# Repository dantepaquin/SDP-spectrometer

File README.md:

# SDP-Spectrometer

This is the joint repository for the hardware and software for the UCSC EE SDP 2021 Spectrometer. 
The directory *kicad-libraries* contains all of the design files for the hardware, including the schematics, kicad projects, footprint & symbol libraries, and gerbers.
The directory *microcontroller-libraries* contains all of the software used by our spectrometer.

## Kicad Libraries
In our design, we used [KiCad v5.1.0](https://www.kicad.org/blog/2019/03/KiCad-5.1.0-Release/) to create libraries for footprints, symbols, schematics, and pcbs. Currently, the initial designs are in their first revision, and we have fabricated prototypes to be tested.

While our design uses five separate boards connected with wires, all designs are located within a single KiCad project, "main.pro."

### Overview of directories:
#### Adafruit-PowerBoost-1000C-master/
Our design uses an existing power delivery board, and this folder contains the physical design documents that we referenced and used in our own.

#### Backup/
An almost-empty folder used for managing local backups and versioining. Can be removed.

#### RN4678dev/
This contains a kicad project and its design files for a development board, opening the SMD footprint to machine headers. These are not necessary for the final design.

#### Renders/
This contains PDF views of the current PCBs, shown with a small selection of layers.

#### SC70-Dev/
This is a development board used for the SC70 footprint, allowing breadboard verification of our systems. This contains a kicad project with the scematic and PCB files.

#### Separate/
This directory contains subdirectories for each of the five PCBs of our design, which allowed us to manufacture individual boards rather than the full set. This also includes the gerbers used to manufacture the initial run of boards. 

#### Wiring Diagram/
This was a development project to identify and plan the necessary connections between the components of our design. It exists for reference, and has no physical form.

#### spectrometer_core.pretty/
This is the footprint library directory, implementing the physical dimensions and connections of each device used in our design.

#### fp-lib-table
This file tells KiCad how to associate the symbols in our schematic with the footprints in spectrometer_core.pretty.

#### main-cache.lib
This file keeps track of all of the symbols used in the schematic.

#### main.kicad_pcb
This is the main PCB file, which is used to design and lay out the footprints into their physical form.

#### main.pro
**This is the main project file of the spectrometer.** Opening this with kicad will give you access to design and change the footprints, symbols, schematics, and PCBs of the design.

#### main.sch
This is the main schematic file, used to establish connections between the components of the design.

#### spectrometer_core.bck
This is a local backup of the spectrometer_core.dcm file, and can be removed.

#### spectrometer_core.dcm
This keeps track of any documentation we added to the symbol library.

#### spectrometer_core.lib
This is our main symbol library, used to represent the components as used on our schematic.

#### sym-lib-table
This keeps track of the symbol libraries used in the main project.

## Microcontroller Libraries

Our project uses a [TeensyLC](https://www.pjrc.com/teensy/teensyLC.html) running [Arduino](https://www.arduino.cc/en/software), and was developed in the Arduino IDE. This directory contains the code we were able to complete, and verious sketches of test programs.

### Overview of directories:

#### Bluetooth/
This directory contains the currnent state of the bluetooth library implementation. The files include CircularBuffer.c/h, used for UART communication; RN4678.cpp/h, the main library file for the RN4678 bluetooth module; and RN4678_Command.h, a file containing all of the available bluetooth commands.

#### Examples/
This directory includes arduino sketches used to verify both the hardware and minor software usage in our design. These will allow basic back-and-forth, following PC -> USB -> Teesny -> UART -> RN4678 -> Bluetooth -> Phone

#### TeesnyMain/
This is the main directory of code running on the TeensyLC, TeensyMain.ino, and includes state machines and libraries used in our design.  

#### Adafruit_SSD1306.cpp/h
This is an open library by Adafruit designed for our OLED screen, based on the SSD1306 driver IC.

#### FiniteStateMachine.cpp/h
This is an old backup of the driving state machine of our microcontroller. The updated version is in TeensyMain/

#### LED.cpp/h
These files are basic LED drivers for arduino, and can be ignored.

#### RN4678_Command.h
This is a backup of the same file located in Bluetooth/. Both files include usage documentation inside

#### TeensyMain.ino
This is an old backup of the main arduino sketch within TeensyMain/, and can be ignored.

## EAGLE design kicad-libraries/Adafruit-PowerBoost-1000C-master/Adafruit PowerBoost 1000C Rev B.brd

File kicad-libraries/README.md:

# Repository for KiCad Libraries and design

Individual design files (footprints & symbols) will go into part-specific subfolders in the "Separate" folder

KiCad organization basics:  
.LIB files store SCHEMATIC SYMBOLS  
.PRETTY folders store FOOTPRINT MODELS  
The two should be associated in their current form. 

Further work includes building basic building-block circuits so that integration is easier later on.

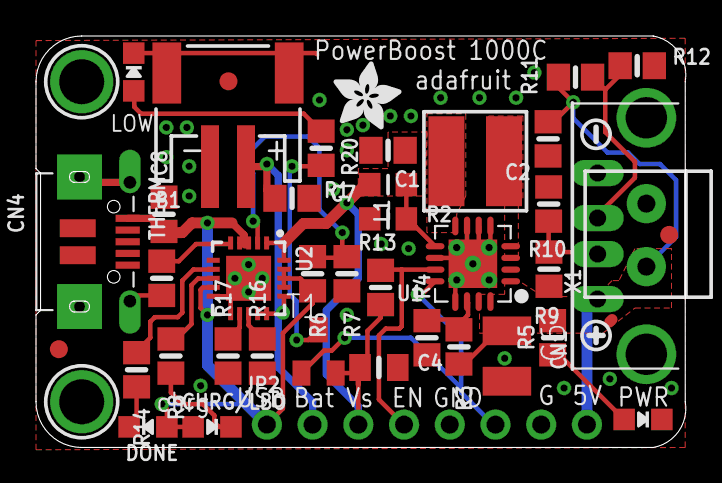
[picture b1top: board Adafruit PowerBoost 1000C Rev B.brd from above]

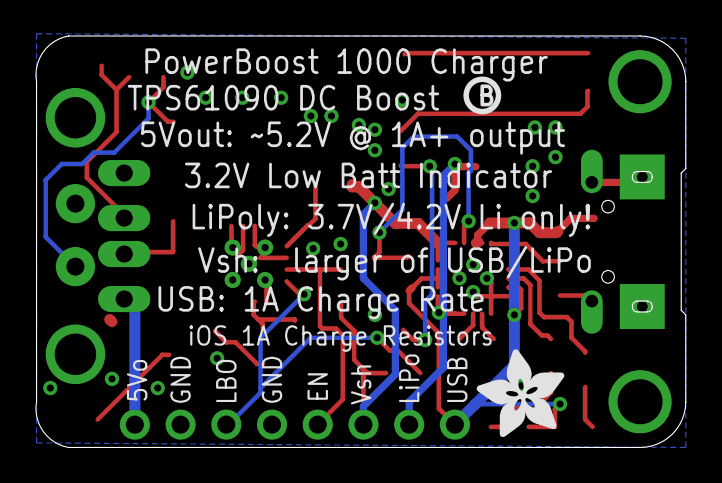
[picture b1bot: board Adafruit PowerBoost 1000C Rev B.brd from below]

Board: 2 copper layers, 36.1 x 22.9 mm, 47 parts (2 on the bottom side), 23 nets.

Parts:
B1: JST 2-PH; JSTPH2
C1, C7, C8: 10uF; 0805-NO
C2: 2.2uF; 0805-NO
C4: 0.1uF; 0805_10MGAP
C6: 100uF; C1210
CHRG/LBO: ORANGE; CHIPLED_0805_NOOUTLINE
CN1: USBA_FEMALE; USB_HOST-PTH
CN4: MicroUSB; 4UCONN_20329
DONE: GREEN; CHIPLED_0805_NOOUTLINE
FID1, FID2, FID3: FIDUCIAL""; FIDUCIAL_1MM
JP2: 1X08_ROUND
L1: 6.8uH; INDUCTOR_5X5MM_TDK_VLC5045
LED1: RED; CHIPLED_0805_NOOUTLINE
LED2: BLUE; CHIPLED_0805_NOOUTLINE
R1: 1.87M; _0805MP
R2: 340K; _0805MP
R3: 1.87M; 0805-NO
R4, R13: 200K; 0805-NO
R5, R8, R14, R20: 1K; 0805-NO
R6: 270K; 0805-NO
R7, R17: 100K; 0805-NO
R9: 43K; 0805-NO
R10: 49.9K; 0805-NO
R11: 75K 1%; 0805-NO
R12: 49.9K 1%; 0805-NO
R16: 1.0K; 0805-NO
T1: MMUN2133LT1G; SC59-BEC
THERM: 15K; 0805-NO
U1: TPS61090RSAR; PVQFN-16
U2: MCP73871; QFN20_4MM
U$10, U$11: MOUNTINGHOLE2.5; MOUNTINGHOLE_2.5_PLATED
U$12: PCBFEAT-REV-040
U$25: SYMBOL_PLUS
U$26: SYMBOL_MINUS
U$28: ADAFRUIT_5MM
U$45: ADAFRUIT_3.5MM
X1: TERMBLOCK_1X2-3.5MM

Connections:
5.0V: C2.1, C6.1, CN1.VBUS, JP2.8, R3.2, R5.1, R9.2, R11.2, U1.1, U1.15, U1.16, X1.2
D+: CN1.D+, R11.1, R12.1
D-: CN1.D-, R9.1, R10.1
ENABLE: JP2.4, R13.2, U1.11
GND: B1.1, C1.2, C2.2, C4.2, C6.2, C7.2, C8.2, CN1.GND, CN4.BASE@1, CN4.BASE@2, CN4.GND, CN4.SPRT@1, CN4.SPRT@2, CN4.SPRT@3, CN4.SPRT@4, JP2.5, JP2.7, LED1.C, LED2.C, R2.1, R4.1, R7.2, R10.2, R12.2, R16.1, R17.1, THERM.1, U1.5, U1.6, U1.7, U1.10, U1.13, U1.P$18, U1.P$19, U1.P$20, U1.P$21, U1.P$22, U1.THERMAL, U2.P$10, U2.P$11, U2.P$21, X1.1
LBO: JP2.6, T1.B, U1.12
unnamed: L1.P$2, U1.3, U1.4
unnamed: LED1.A, R20.1
unnamed: R1.1, R2.2, U1.9
unnamed: LED2.A, R5.2
unnamed: R3.1, R4.2, U1.14
unnamed: R20.2, T1.C
unnamed: R6.1, R7.1, U2.P$2
unnamed: DONE.C, R14.2
unnamed: R14.1, U2.P$7
unnamed: THERM.2, U2.P$5
unnamed: R8.1, U2.P$8
unnamed: CHRG/LBO.C, R8.2
unnamed: R17.2, U2.P$12
unnamed: R16.2, U2.P$13
VBAT: C1.1, C4.1, JP2.3, L1.P$1, R1.2, R13.1, T1.E, U1.8, U2.P$1, U2.P$20
VBUS: C8.1, CHRG/LBO.A, CN4.VBUS, DONE.A, JP2.1, R6.2, U2.P$3, U2.P$4, U2.P$9, U2.P$17, U2.P$18, U2.P$19
VLIPO: B1.2, C7.1, JP2.2, U2.P$14, U2.P$15, U2.P$16

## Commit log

2021-07-30 added project files
2021-07-30 messed up smth
2021-07-30 added all project files
2021-08-14 Delete RN4678.h
    does not belong
2021-08-14 Update README.md
    Formatting

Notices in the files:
parts and their libraries:
microbuilder: This work is placed in the public domain, and may be freely used for commercial and non-commercial work with the following conditions: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
